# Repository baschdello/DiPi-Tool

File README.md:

# DiPi-Tool
Description will follow soon...

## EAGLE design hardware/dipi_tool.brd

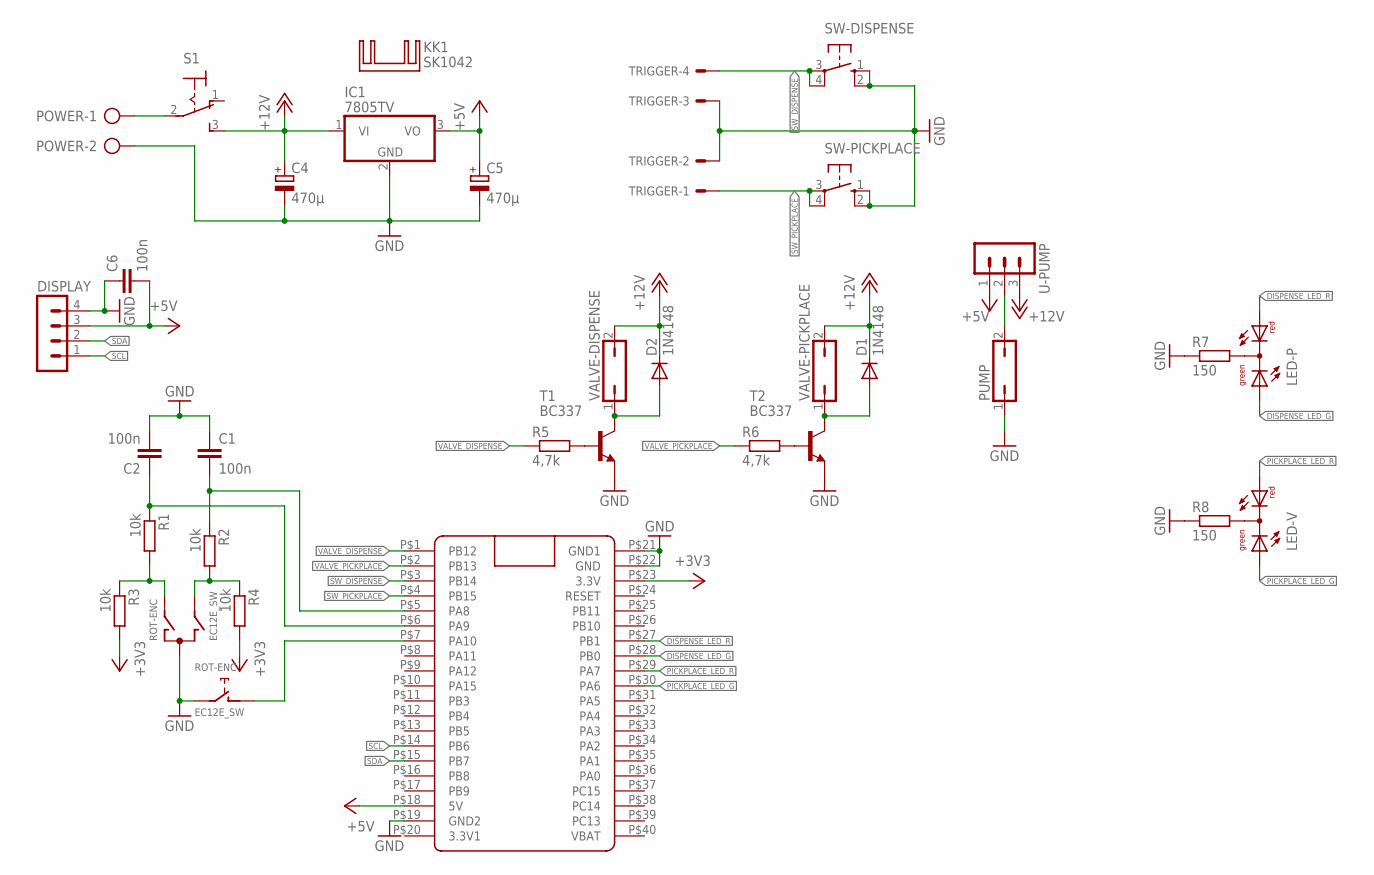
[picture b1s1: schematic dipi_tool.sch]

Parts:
C1, C2, C6: 100n; C1206
C4: 470µ; E3,5-10
C5: 470µ; E2,5-7
D1, D2: 1N4148; DO35-7
DISPLAY: MA04-1
IC1: 7805TV; TO220V
KK1: SK1042; CUSTOM1-PAD
LED-P: DUOLED-RG-C"; DUOLED-C-3MM
LED-V: DUOLED-RG-C"; DUOLED-C-3MM
POWER: AK500/2
PUMP: JP1Q; JP1
R1, R2, R3, R4: 10k; R1206
R5, R6: 4,7k; 0204V
R7, R8: 150; 0204V
ROT-ENC: EC12E_SW; ALPS_EC12E_SW
S1: M9040P
SW-DISPENSE: 10-XX; B3F-10XX
SW-PICKPLACE: 10-XX; B3F-10XX
T1, T2: BC337; TO92
TRIGGER: 22-27-2041-04; 6410-04
U$1: BLUE_PILL
U-PUMP: MA03-1
VALVE-DISPENSE: JP1Q; JP1
VALVE-PICKPLACE: JP1Q; JP1

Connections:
+3V3: R3.2, R4.2, U$1.P$23 (3.3V)
+5V: C5.+, C6.2, DISPLAY.3, IC1.3 (VO), U$1.P$18 (5V), U-PUMP.1
+12V: C4.+, D1.C, D2.C, IC1.1 (VI), S1.3 (S), U-PUMP.3, VALVE-DISPENSE.2, VALVE-PICKPLACE.2
DISPENSE_LED_G: LED-P.1 (AG), U$1.P$28 (PB0)
DISPENSE_LED_R: LED-P.3 (AR), U$1.P$27 (PB1)
GND: C1.1, C2.2, C4.-, C5.-, C6.1, DISPLAY.4, IC1.2 (GND), POWER.2, PUMP.1, R7.1, R8.1, ROT-ENC.C, ROT-ENC.E (2), SW-DISPENSE.1 (S), SW-DISPENSE.2 (S1), SW-PICKPLACE.1 (S), SW-PICKPLACE.2 (S1), T1.1 (E), T2.1 (E), TRIGGER.2, TRIGGER.3, U$1.P$19 (GND2), U$1.P$21 (GND1), U$1.P$22 (GND)
unnamed: R2.2, R4.1, ROT-ENC.B
unnamed: R5.2, T1.2 (B)
unnamed: C2.1, R1.1, U$1.P$6 (PA9)
unnamed: C1.2, R2.1, U$1.P$5 (PA8)
unnamed: R1.2, R3.1, ROT-ENC.A
unnamed: R6.2, T2.2 (B)
unnamed: D2.A, T1.3 (C), VALVE-DISPENSE.1
unnamed: ROT-ENC.D (1), U$1.P$7 (PA10)
unnamed: D1.A, T2.3 (C), VALVE-PICKPLACE.1
unnamed: POWER.1, S1.2
unnamed: LED-P.2 (C), R7.2
unnamed: LED-V.2 (C), R8.2
unnamed: PUMP.2, U-PUMP.2
PICKPLACE_LED_G: LED-V.1 (AG), U$1.P$30 (PA6)
PICKPLACE_LED_R: LED-V.3 (AR), U$1.P$29 (PA7)
SCL: DISPLAY.1, U$1.P$14 (PB6)
SDA: DISPLAY.2, U$1.P$15 (PB7)
SW_DISPENSE: SW-DISPENSE.3, SW-DISPENSE.4 (P1), TRIGGER.4, U$1.P$3 (PB14)
SW_PICKPLACE: SW-PICKPLACE.3, SW-PICKPLACE.4 (P1), TRIGGER.1, U$1.P$4 (PB15)
VALVE_DISPENSE: R5.1, U$1.P$1 (PB12)
VALVE_PICKPLACE: R6.1, U$1.P$2 (PB13)

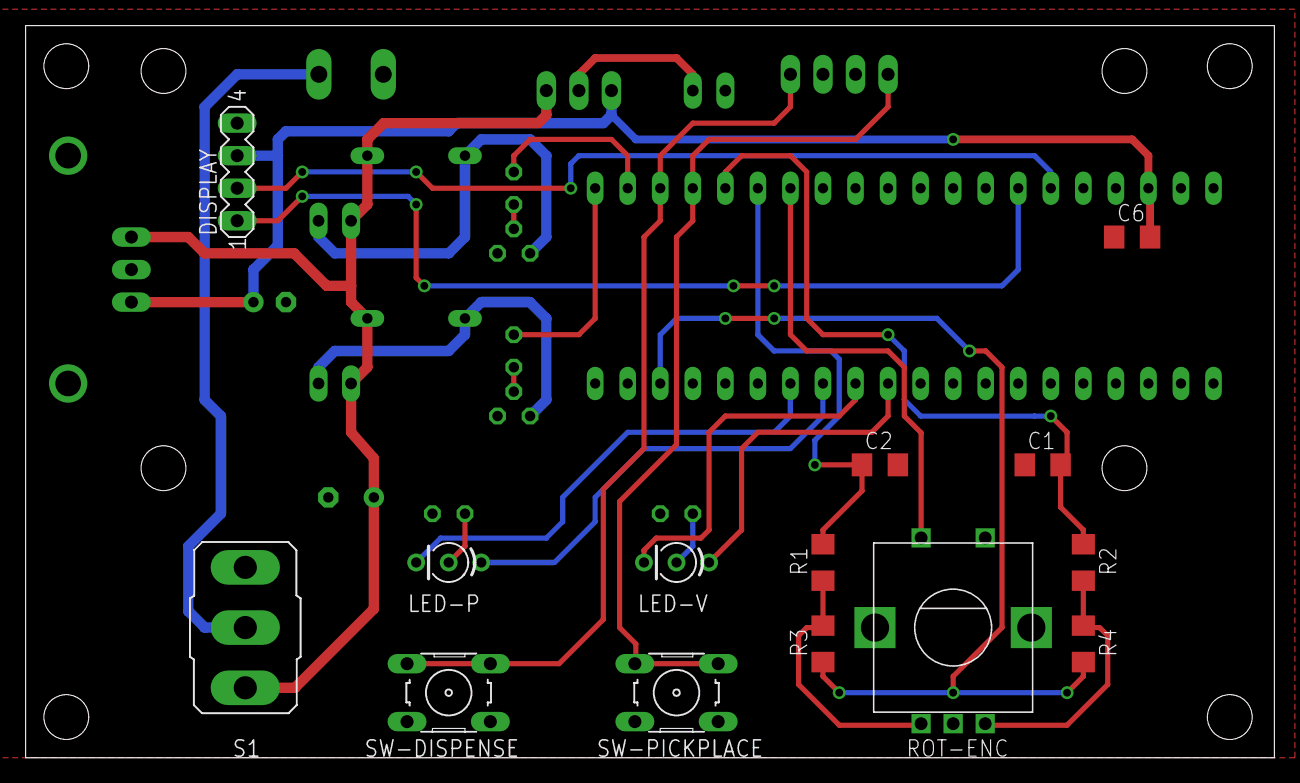
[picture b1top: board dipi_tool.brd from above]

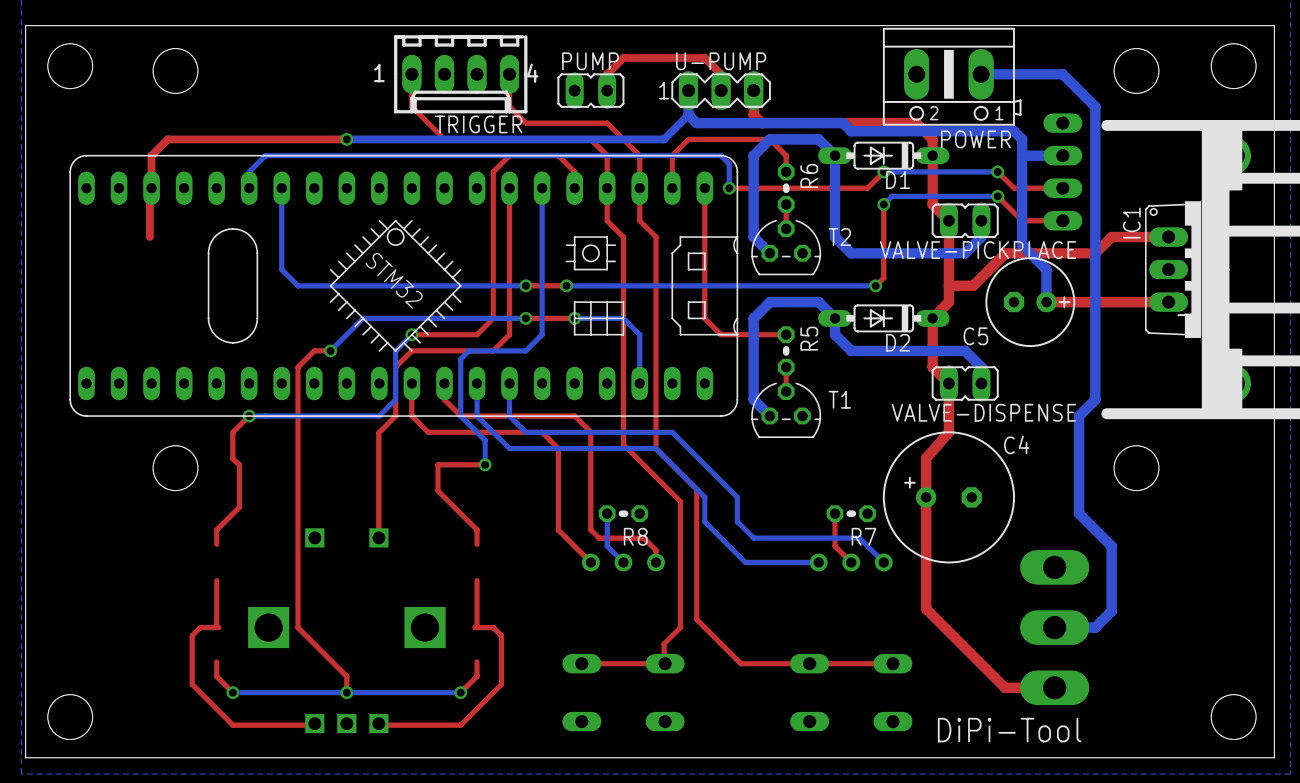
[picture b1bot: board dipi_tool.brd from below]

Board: 2 copper layers, 97.5 x 57.1 mm, 33 parts (19 on the bottom side), 27 nets.

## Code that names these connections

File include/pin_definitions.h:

#ifndef _PIN_DEFINITIONS_H_
#define _PIN_DEFINITIONS_H_

#define SWITCH_DISPENSE       PB14
#define SWITCH_PICKPLACE      PB15
#define SWITCH_ROTARY         PA10

#define VALVE_DISPENSE        PB12
#define VALVE_PICKPLACE       PB13

#define LED_RED_DISPENSE      PB1
#define LED_GREEN_DISPENSE    PB0
#define LED_RED_PICKPLACE     PA7
#define LED_GREEN_PICKPLACE   PA6

#define ROTENC_A              PA9
#define ROTENC_B              PA8

#define SDA                   PB7
#define SCL                   PB6


#endif
